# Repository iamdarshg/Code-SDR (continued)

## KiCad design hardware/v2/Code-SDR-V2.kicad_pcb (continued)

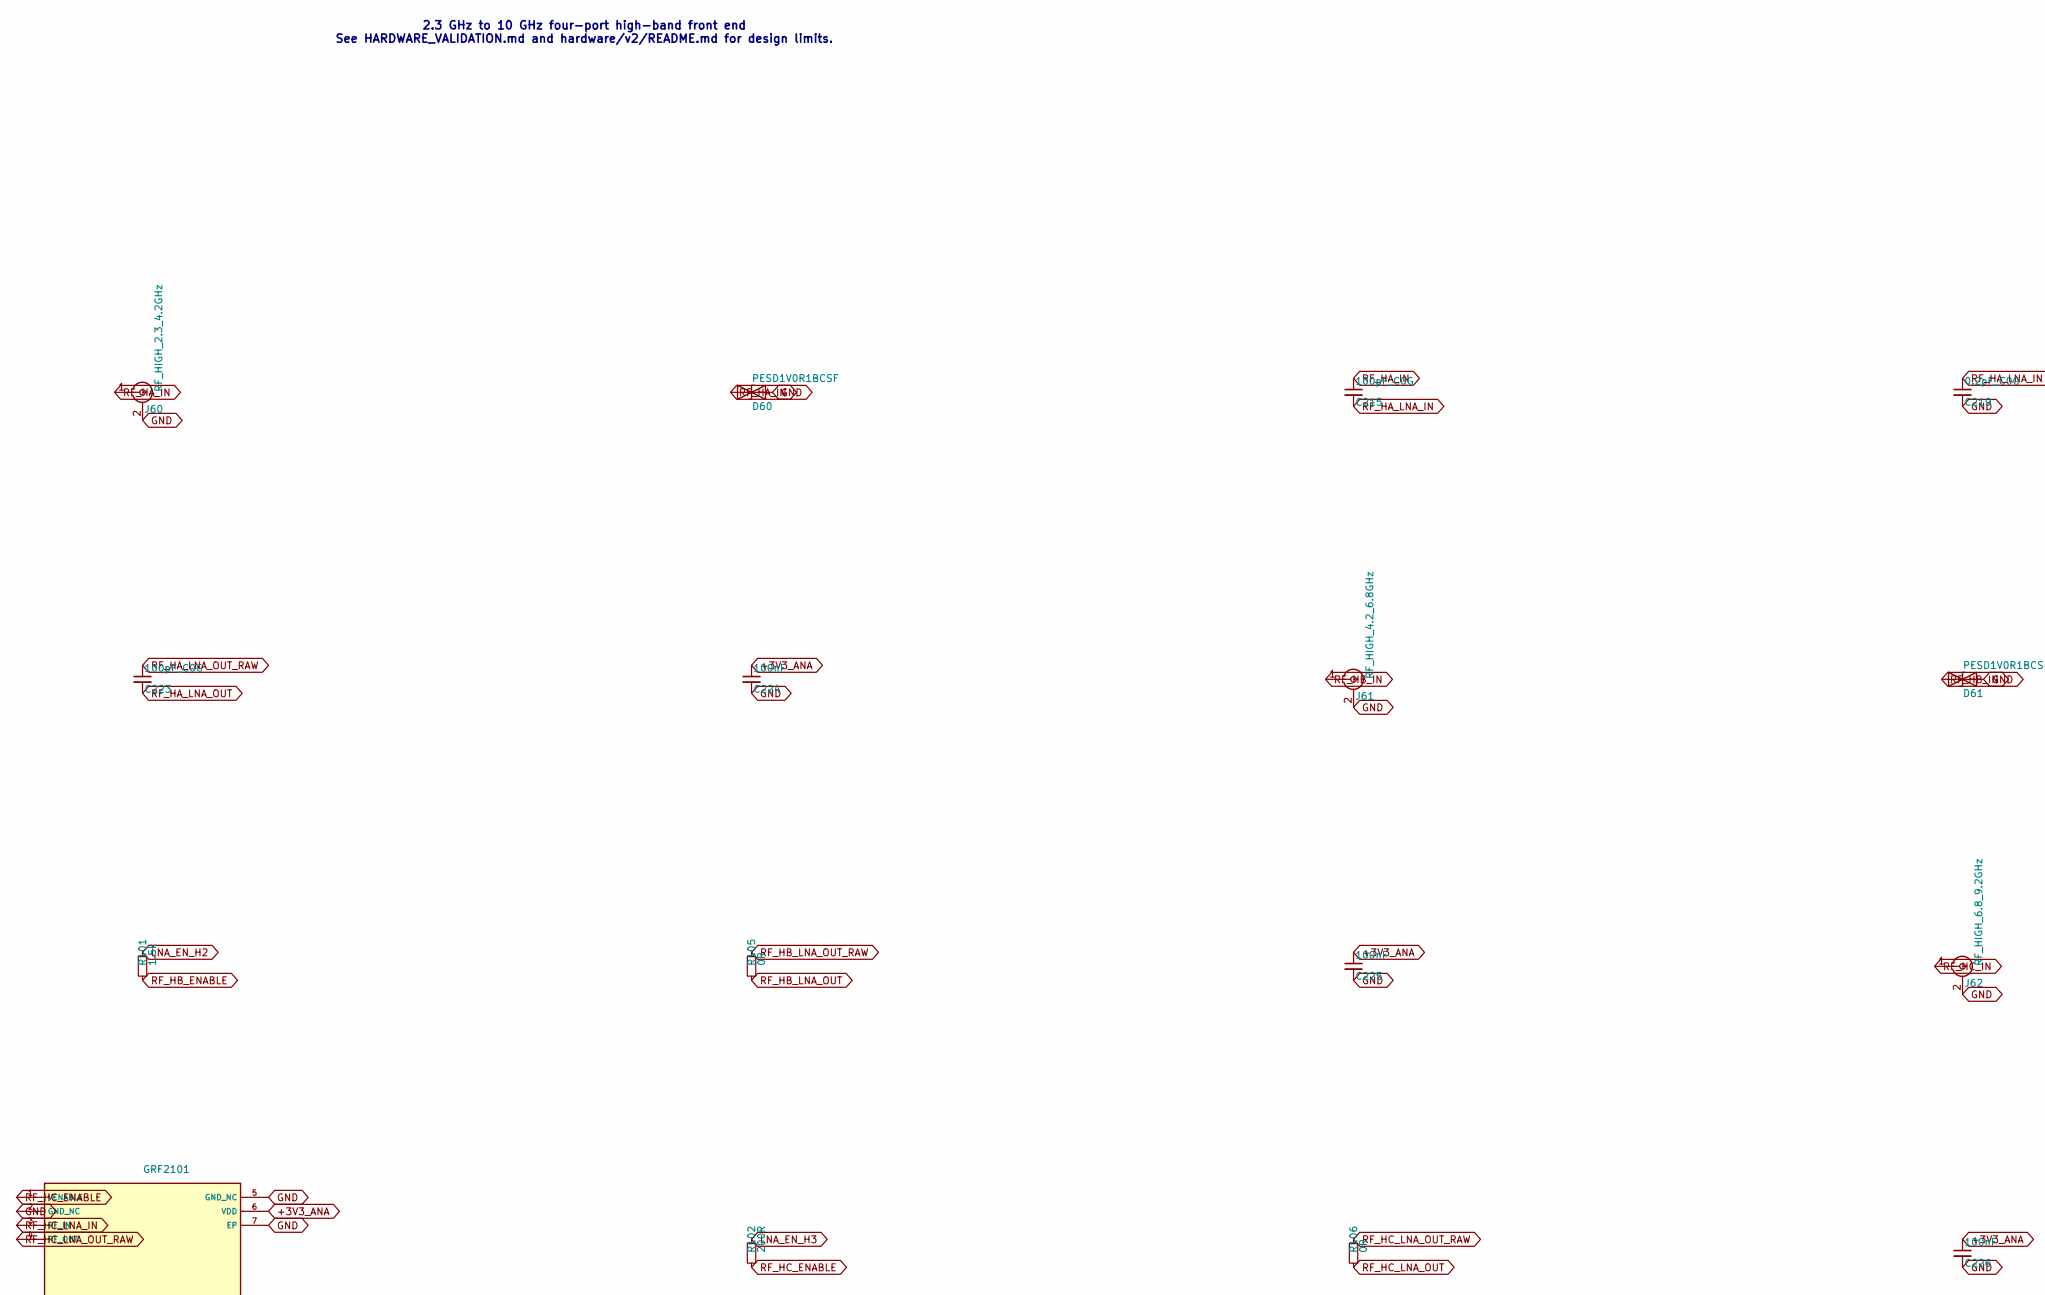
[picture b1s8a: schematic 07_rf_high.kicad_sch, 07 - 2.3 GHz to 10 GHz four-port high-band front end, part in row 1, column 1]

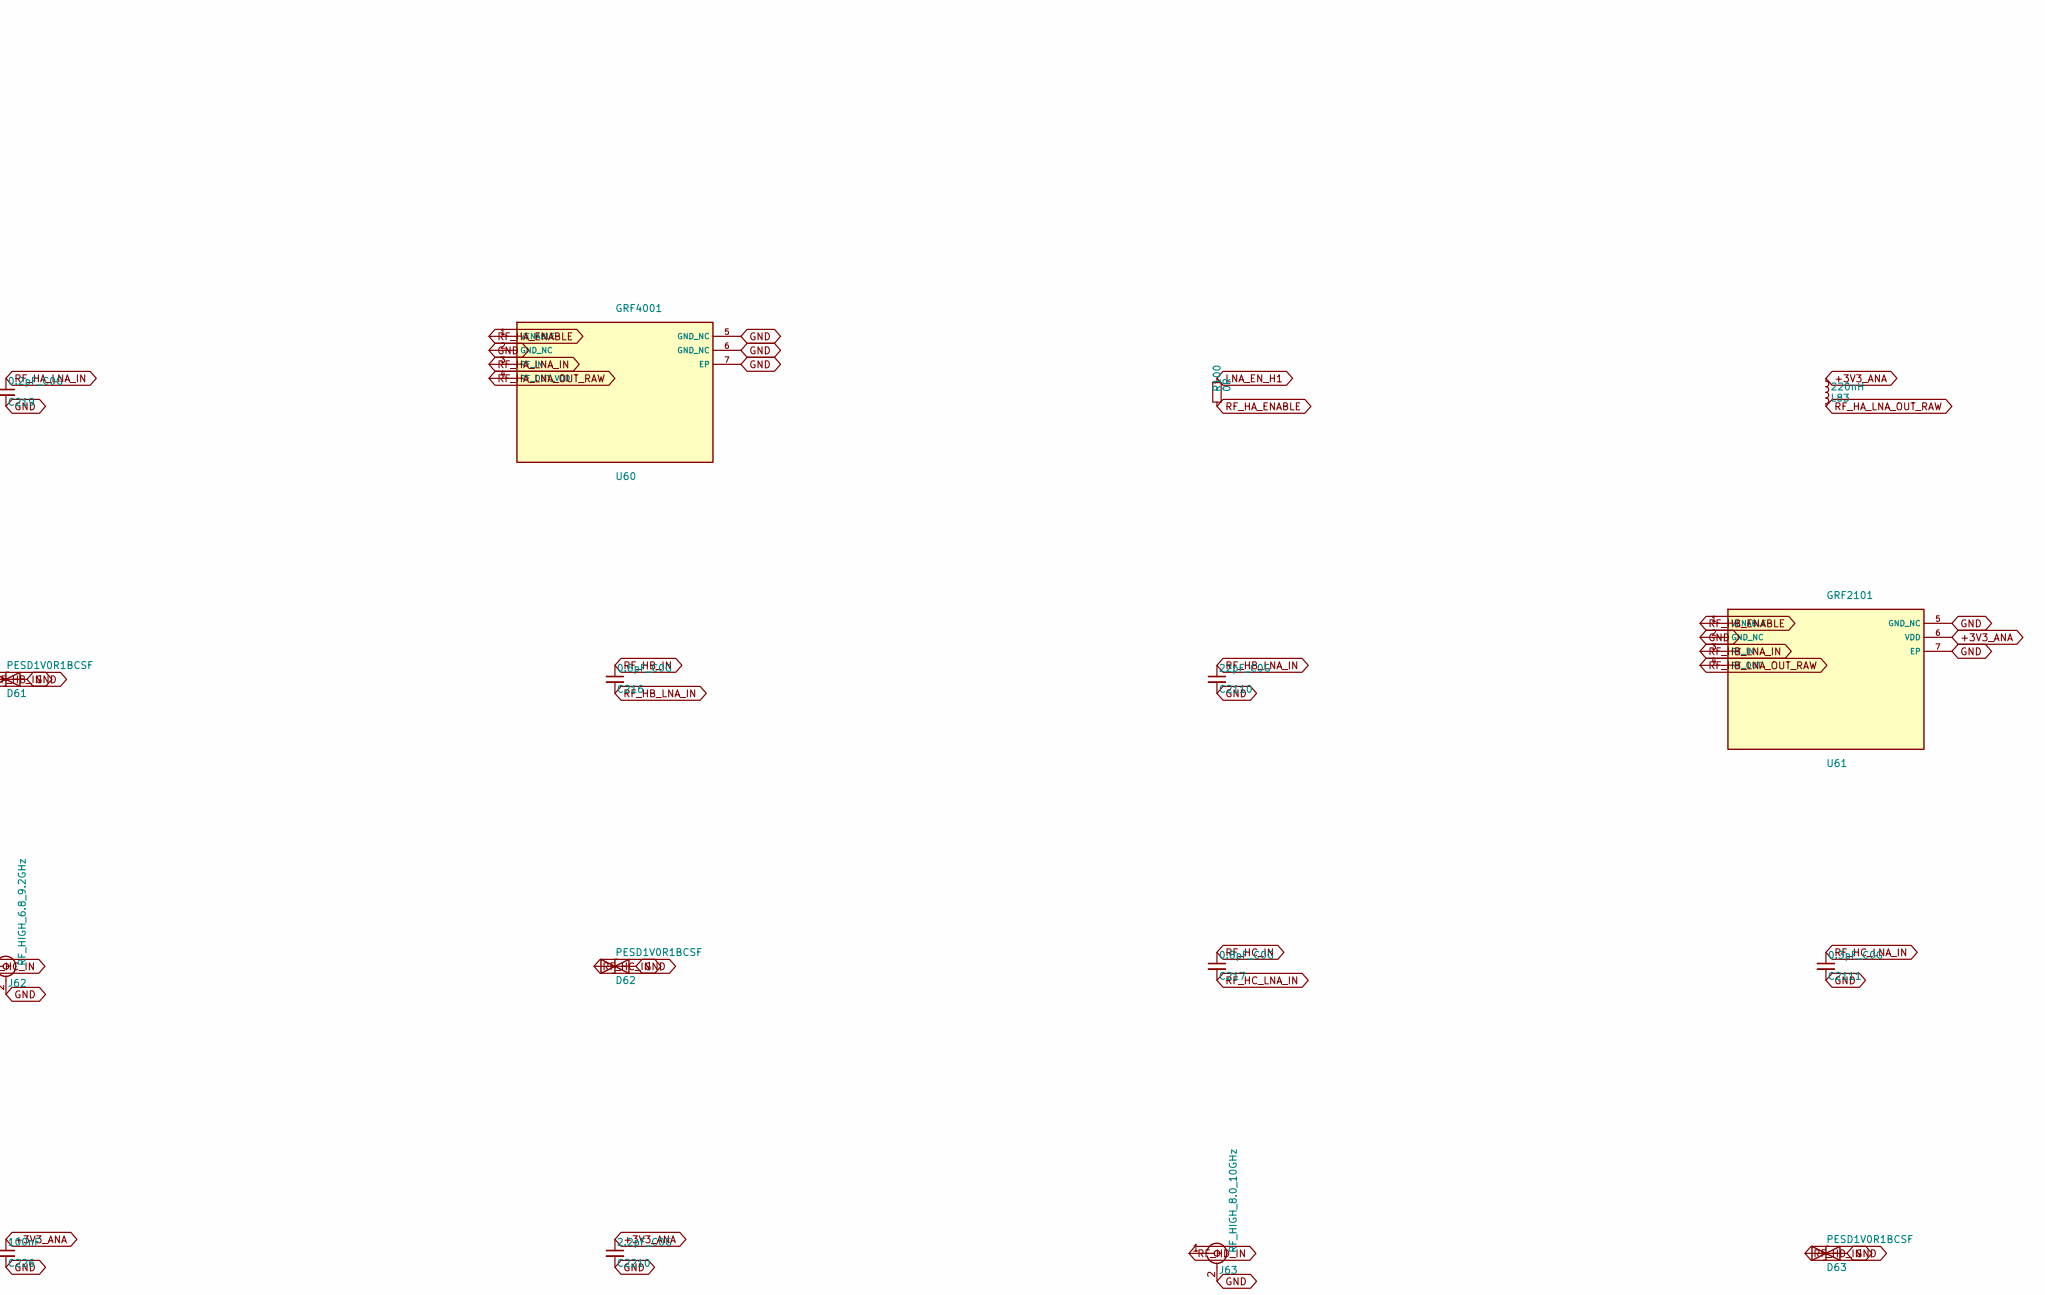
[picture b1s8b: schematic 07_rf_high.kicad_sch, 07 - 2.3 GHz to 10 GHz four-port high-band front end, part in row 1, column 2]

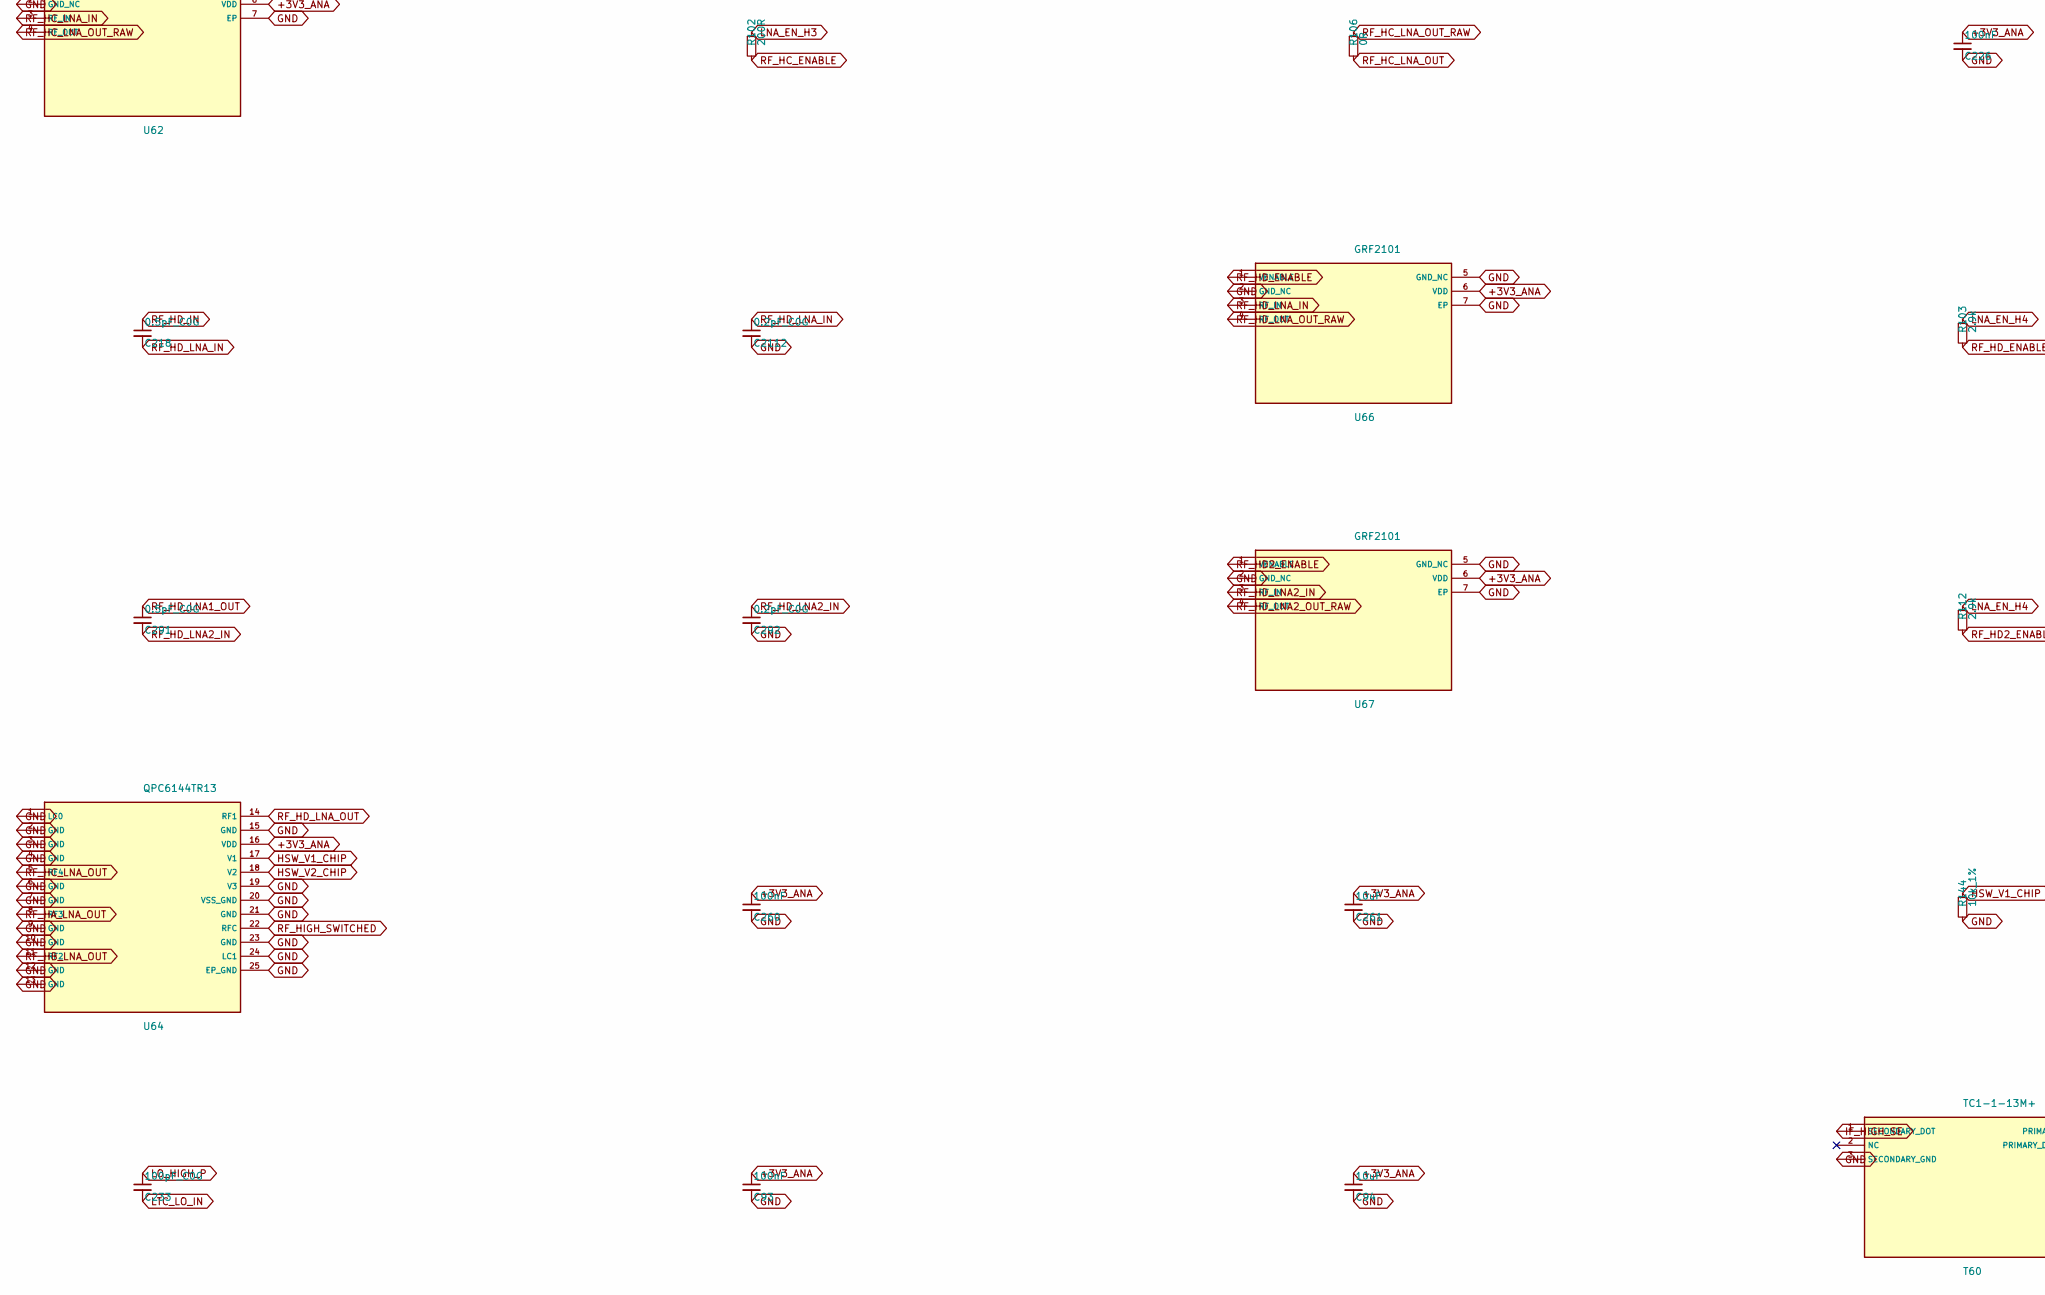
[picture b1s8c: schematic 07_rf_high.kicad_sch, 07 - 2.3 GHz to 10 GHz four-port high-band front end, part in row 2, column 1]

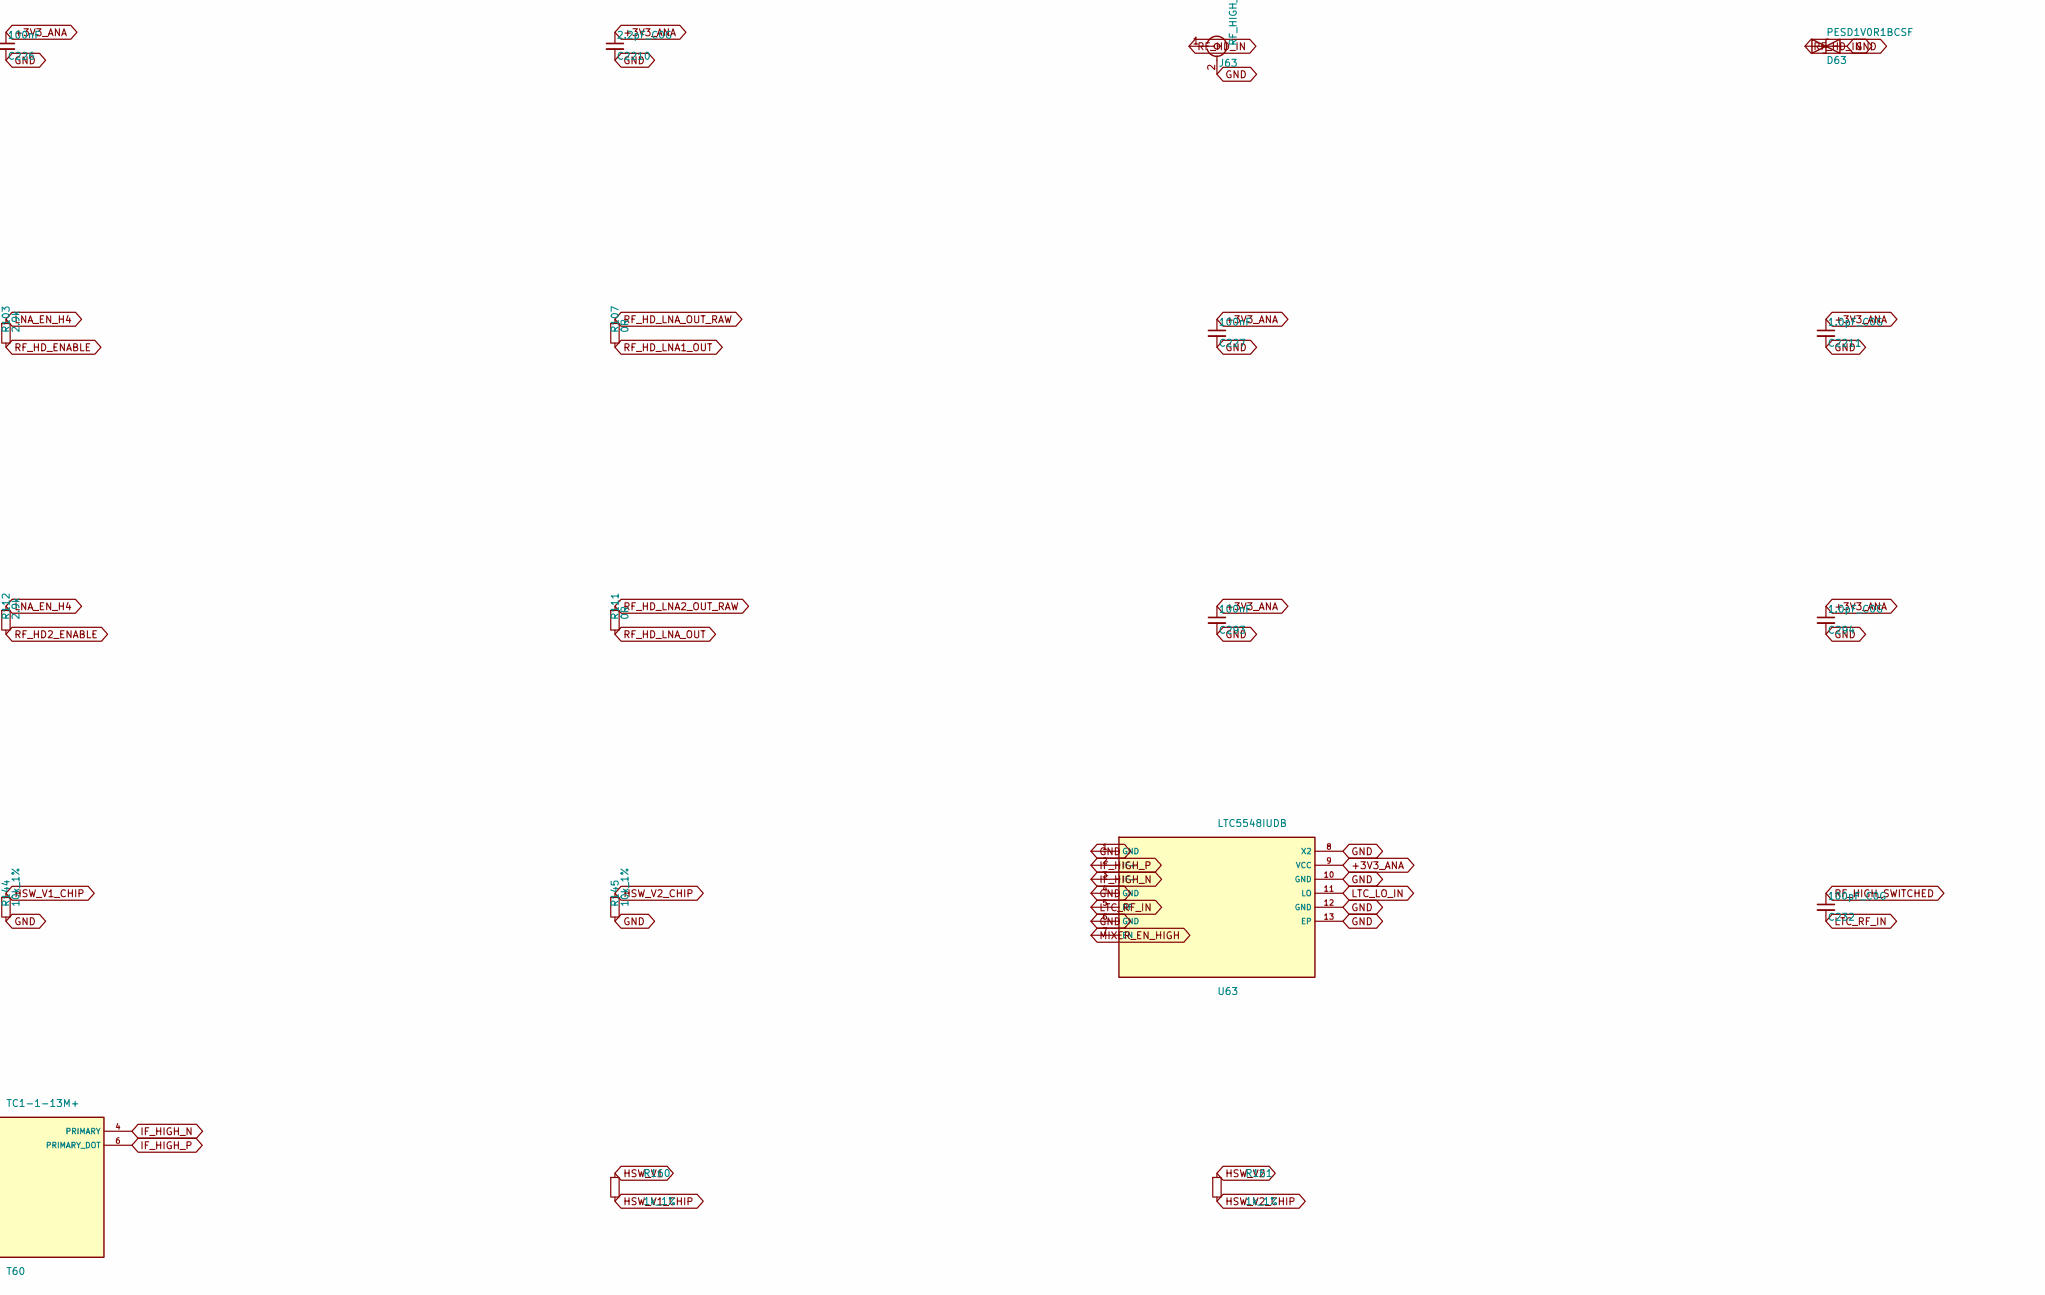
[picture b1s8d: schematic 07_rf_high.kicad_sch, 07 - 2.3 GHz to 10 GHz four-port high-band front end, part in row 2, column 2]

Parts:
C93, C224, C225, C226, C227, C260, C293: 100nF; C_0402_1005Metric
C94, C261: 10uF; C_0805_2012Metric
C215, C223, C232, C233: 100pF_C0G; C_0201_0603Metric
C216: 0.6pF_C0G; C_0201_0603Metric
C217: 0.8pF_C0G; C_0201_0603Metric
C218, C291: 0.5pF_C0G; C_0201_0603Metric
C219, C292, C2112: 0.2pF_C0G; C_0201_0603Metric
C294, C2211: 1.0pF_C0G; C_0201_0603Metric
C2110: 22pF_C0G; C_0201_0603Metric
C2111: 0.3pF_C0G; C_0201_0603Metric
C2210: 2.2pF_C0G; C_0201_0603Metric
D60, D61, D62, D63: PESD1V0R1BCSF; SOD962-2_DSN0603
J60: RF_HIGH_2.3_4.2GHz; SMA_Molex_73251-1153_EdgeMount_Horizontal
J61: RF_HIGH_4.2_6.8GHz; SMA_Molex_73251-1153_EdgeMount_Horizontal
J62: RF_HIGH_6.8_9.2GHz; SMA_Molex_73251-1153_EdgeMount_Horizontal
J63: RF_HIGH_8.0_10GHz; SMA_Molex_73251-1153_EdgeMount_Horizontal
L83: 220nH; L_0603_1608Metric_Pad1.05x0.95mm_HandSolder
R100, R105, R106, R107, R111: 0R; R_0201_0603Metric
R101: 1.5k; R_0201_0603Metric
R102: 200R; R_0201_0603Metric
R103, R112: 2.9k; R_0201_0603Metric
R144, R145: 10k_1%; R_0402_1005Metric
R160, R161: 1k_1%; R_0402_1005Metric
T60: TC1-1-13M+; Transformer_MiniCircuits_AT224-1A
U60: GRF4001; GRF_DFN6_1.5x1.5mm
U61, U62, U66, U67: GRF2101; GRF_DFN6_1.5x1.5mm
U63: LTC5548IUDB; DFN-12-1EP_3x2mm_P0.5mm
U64: QPC6144TR13; QPC6144_LGA24_4x4mm

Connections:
+3V3_ANA: C93.1, C94.1, C224.1, C225.1, C226.1, C227.1, C260.1, C261.1, C293.1, C294.1, C2210.1, C2211.1, L83.1, U61.6 (VDD), U62.6 (VDD), U63.9 (VCC), U64.16 (VDD), U66.6 (VDD), U67.6 (VDD); also elsewhere on the board
HSW_V1: R160.1; also elsewhere on the board
HSW_V1_CHIP: R144.1, R160.2, U64.17 (V1)
HSW_V2: R161.1; also elsewhere on the board
HSW_V2_CHIP: R145.1, R161.2, U64.18 (V2)
IF_HIGH_N: T60.4 (PRIMARY), U63.3 (IF-)
IF_HIGH_P: T60.6 (PRIMARY_DOT), U63.2 (IF+)
IF_HIGH_SE: T60.1 (SECONDARY_DOT); also elsewhere on the board
LNA_EN_H1: R100.1; also elsewhere on the board
LNA_EN_H2: R101.1; also elsewhere on the board
LNA_EN_H3: R102.1; also elsewhere on the board
LNA_EN_H4: R103.1, R112.1; also elsewhere on the board
LO_HIGH_P: C233.1; also elsewhere on the board
LTC_LO_IN: C233.2, U63.11 (LO)
LTC_RF_IN: C232.2, U63.5 (RF)
MIXER_EN_HIGH: U63.7 (EN); also elsewhere on the board
RF_HA_ENABLE: R100.2, U60.1 (VENABLE)
RF_HA_IN: C215.1, D60.1 (A1), J60.1 (In)
RF_HA_LNA_IN: C215.2, C219.1, U60.3 (RF_IN)
RF_HA_LNA_OUT: C223.2, U64.8 (RF3)
RF_HA_LNA_OUT_RAW: C223.1, L83.2, U60.4 (RF_OUT_VDD)
RF_HB_ENABLE: R101.2, U61.1 (VENABLE)
RF_HB_IN: C216.1, D61.1 (A1), J61.1 (In)
RF_HB_LNA_IN: C216.2, C2110.1, U61.3 (RF_IN)
RF_HB_LNA_OUT: R105.2, U64.11 (RF2)
RF_HB_LNA_OUT_RAW: R105.1, U61.4 (RF_OUT)
RF_HC_ENABLE: R102.2, U62.1 (VENABLE)
RF_HC_IN: C217.1, D62.1 (A1), J62.1 (In)
RF_HC_LNA_IN: C217.2, C2111.1, U62.3 (RF_IN)
RF_HC_LNA_OUT: R106.2, U64.5 (RF4)
RF_HC_LNA_OUT_RAW: R106.1, U62.4 (RF_OUT)
RF_HD2_ENABLE: R112.2, U67.1 (VENABLE)
RF_HD_ENABLE: R103.2, U66.1 (VENABLE)
RF_HD_IN: C218.1, D63.1 (A1), J63.1 (In)
RF_HD_LNA1_OUT: C291.1, R107.2
RF_HD_LNA2_IN: C291.2, C292.1, U67.3 (RF_IN)
RF_HD_LNA2_OUT_RAW: R111.1, U67.4 (RF_OUT)
RF_HD_LNA_IN: C218.2, C2112.1, U66.3 (RF_IN)
RF_HD_LNA_OUT: R111.2, U64.14 (RF1)
RF_HD_LNA_OUT_RAW: R107.1, U66.4 (RF_OUT)
RF_HIGH_SWITCHED: C232.1, U64.22 (RFC)

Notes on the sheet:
2.3 GHz to 10 GHz four-port high-band front end See HARDWARE_VALIDATION.md and hardware/v2/README.md for design limits.

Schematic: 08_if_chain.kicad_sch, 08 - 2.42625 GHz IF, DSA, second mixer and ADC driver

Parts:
C100, C101, C105, C254, C255, C256, C284: 100nF; C_0402_1005Metric
C102: 1nF_C0G; C_0402_1005Metric
C106: 10uF; C_0805_2012Metric
C234, C235, C236, C237, C238, C245: 100pF_C0G; C_0201_0603Metric
C246: 1.0pF_C0G; C_0201_0603Metric
C247: 1uF; C_0603_1608Metric
C262, C268: 51pF_C0G; C_0402_1005Metric
C264, C266: 56pF_C0G; C_0402_1005Metric
FL70: QPQ1909TR13; QPQ1909_1.4x1.2mm
L84, L97: 33nH; L_0402_1005Metric_Pad0.77x0.64mm_HandSolder
L85, L86: 2.2uH; L_0603_1608Metric_Pad1.05x0.95mm_HandSolder
L87, L88, L95, L96: 200nH; L_0603_1608Metric_Pad1.05x0.95mm_HandSolder
L89, L90, L93, L94: 360nH; L_0603_1608Metric_Pad1.05x0.95mm_HandSolder
L91, L92: 390nH; L_0603_1608Metric_Pad1.05x0.95mm_HandSolder
R70, R81: 499R_1%; R_0402_1005Metric
R71: 3.0R_1%; R_0402_1005Metric
R72: 33R_1%; R_0402_1005Metric
R73, R74: 25R_1%; R_0402_1005Metric
R75, R76, R77, R78: 10k_1%; R_0402_1005Metric
R79, R80: 100R_1%; R_0402_1005Metric
R146: 100k; R_0402_1005Metric
T70: 2450BL15B0100001E; Johanson_0805_6P_Balun
U70: BGS12WN6E6327; Infineon_TSNP6_1.1x0.7mm
U71, U75: GRF2013; GRF_DFN6_1.5x1.5mm
U72: PE4312C-Z; QFN-20-1EP_4x4mm_P0.5mm_EP2.6x2.6mm_ThermalVias
U73: LT5560EDD; DFN-8-1EP_3x3mm_P0.5mm_EP1.65x2.38mm_ThermalVias
U74: AD8351ARMZ; MSOP-10_3x3mm_P0.5mm

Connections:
+3V3_ANA: C102.1, C247.1, L85.1, L86.1, R75.1, U73.2 (EN), U73.7 (VCC); also elsewhere on the board
+5V_RF: C100.1, C105.1, C106.1, C284.1, L84.1, L97.1, R70.1, R81.1, U74.1 (PWUP), U74.9 (VPOS); also elsewhere on the board
AD8351_IN_N: C255.2, U74.4 (INLO)
AD8351_IN_P: C254.2, U74.3 (INHI)
AD8351_OUT_N: R74.1, U74.7 (OPLO)
AD8351_OUT_P: R73.1, U74.8 (OPHI)
AD8351_RGP1: R72.1, U74.2 (RGP1)
AD8351_RGP2: R72.2, U74.5 (RGP2)
ADC_VCM: C256.1, R75.2, R76.1, U74.10 (VOCM)
ADC_VIN_N: R74.2; also elsewhere on the board
ADC_VIN_P: R73.2; also elsewhere on the board
DSA_C16: R78.2, U72.1 (C16)
DSA_CLK: U72.4 (CLOCK); also elsewhere on the board
DSA_DATA: R77.1; also elsewhere on the board
DSA_DATA_PIN: R77.2, U72.3 (DATA)
DSA_LE: U72.5 (LE); also elsewhere on the board
GRF2013B_ENABLE: R81.2, U75.1 (VENABLE)
GRF2013B_RFOUT_VDD: C238.1, L97.2, U75.4 (RF_OUT_VDD)
GRF2013_ENABLE: R70.2, U71.1 (VENABLE)
GRF2013_RFIN: C234.2, U71.3 (RF_IN)
GRF2013_RFOUT_VDD: C235.1, L84.2, U71.4 (RF_OUT_VDD)
IF2_F1_N: C262.2, L88.2, L90.1
IF2_F1_P: C262.1, L87.2, L89.1
IF2_F2_N: C264.2, L90.2, L92.1
IF2_F2_P: C264.1, L89.2, L91.1
IF2_F3_N: C266.2, L92.2, L94.1
IF2_F3_P: C266.1, L91.2, L93.1
IF2_F4_N: C268.2, L94.2, L96.1
IF2_F4_P: C268.1, L93.2, L95.1
IF2_LPF_N: C255.1, L96.2, R80.2
IF2_LPF_P: C254.1, L95.2, R80.1
IF2_N: L86.2, L88.1, R79.2, U73.5 (OUT-)
IF2_P: L85.2, L87.1, R79.1, U73.6 (OUT+)
IF_BAW_OUT: C234.1, FL70.4 (OUT)
IF_DSA_GAINED: C238.2, C245.1
IF_DSA_OUT: C237.2, U75.3 (RF_IN)
IF_GAIN_OUT: C235.2, C236.1
IF_HIGH_SE: U70.1 (RF2); also elsewhere on the board
IF_LOW_SE: U70.3 (RF1); also elsewhere on the board
IF_PATH_SEL: R146.1, U70.6 (CTRL); also elsewhere on the board
IF_SELECTED: FL70.1 (IN), U70.5 (RFC)
LO2_N: U73.1 (LO-); also elsewhere on the board
LO2_P: U73.8 (LO+); also elsewhere on the board
LT_INPUT_CT: R71.1, T70.2 (DC_FEED_RF_GND)
LT_INPUT_SE: C245.2, C246.1, T70.1 (UNBALANCED)
LT_IN_N: T70.4 (BALANCED_2), U73.4 (IN-)
LT_IN_P: T70.3 (BALANCED_1), U73.3 (IN+)
PE4312_RF1: C236.2, U72.2 (RF1)
PE4312_RF2: C237.1, U72.14 (RF2)

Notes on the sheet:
2.42625 GHz IF, DSA, second mixer and ADC driver See HARDWARE_VALIDATION.md and hardware/v2/README.md for design limits.

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
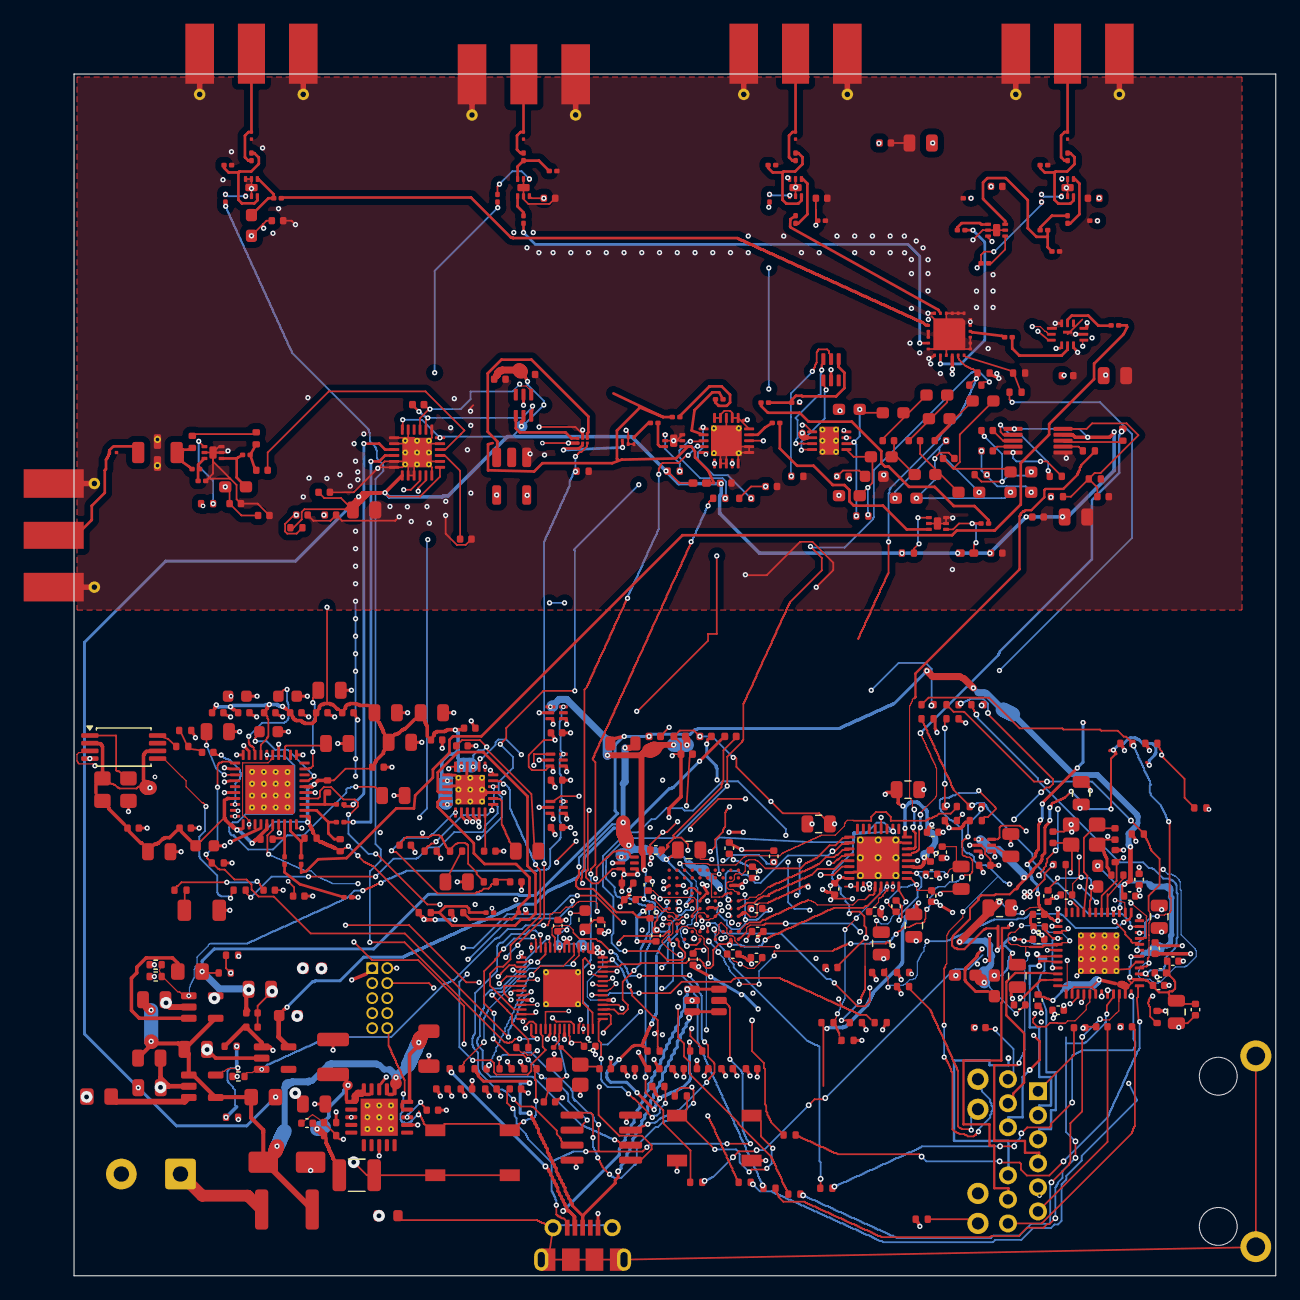
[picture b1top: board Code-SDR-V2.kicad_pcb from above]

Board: 4 copper layers, 101.6 x 101.6 mm, 373 parts (0 on the bottom side), 260 nets.

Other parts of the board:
C340, C341, C342, C343, C344, C347: 100nF; C_0402_1005Metric
C345: 20nF_C0G_5%; C_0805_2012Metric
C346: 47uF_10V_X7R; C_1210_3225Metric
C348: 10nF; C_0402_1005Metric
R154: 30.3k_0.1%; R_0402_1005Metric
R155: 10k_0.1%; R_0402_1005Metric
R157, R159: 120k_1%; R_0402_1005Metric
R158: 100k_1%; R_0402_1005Metric
U5, U6, U7: TPS389033DSER; WSON-6_1.5x1.5mm_P0.5mm
U8, U9: TPS389012DSER; WSON-6_1.5x1.5mm_P0.5mm

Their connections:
+3V3_ANA: C346.1, C348.1, R154.1; also elsewhere on the board
ANA_NR_SS: C347.1; also elsewhere on the board
FPGA_VCCIO0_3V3: U5.1; also elsewhere on the board
FPGA_VCCIO1_3V3: U6.1; also elsewhere on the board
FPGA_VCCIO2_3V3: U7.1; also elsewhere on the board
FPGA_VCC_1V2: U8.1; also elsewhere on the board
PHY_AVDDL_1V2: U9.1; also elsewhere on the board
PHY_RESET_CT: C345.1, U9.5
PHY_RESET_N: U9.6; also elsewhere on the board
